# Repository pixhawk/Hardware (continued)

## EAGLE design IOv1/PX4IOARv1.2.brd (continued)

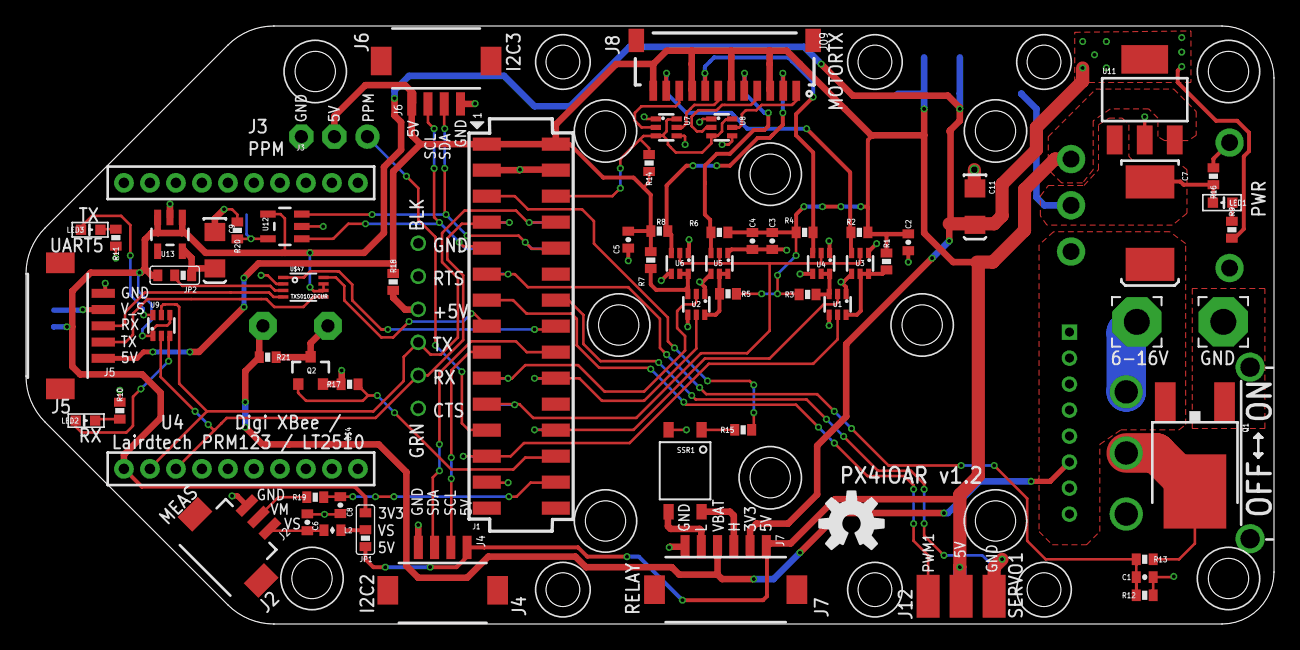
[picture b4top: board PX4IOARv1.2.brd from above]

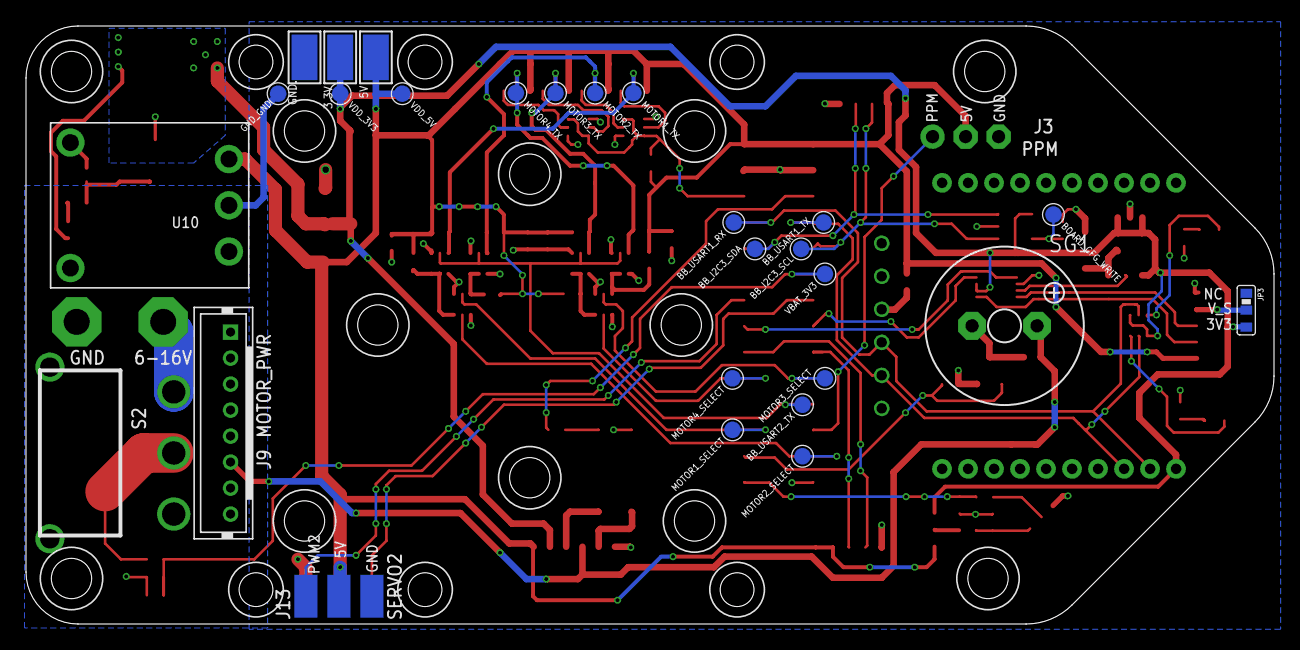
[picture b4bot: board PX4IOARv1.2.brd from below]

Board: 2 copper layers, 96.0 x 46.0 mm, 112 parts (27 on the bottom side), 59 nets.

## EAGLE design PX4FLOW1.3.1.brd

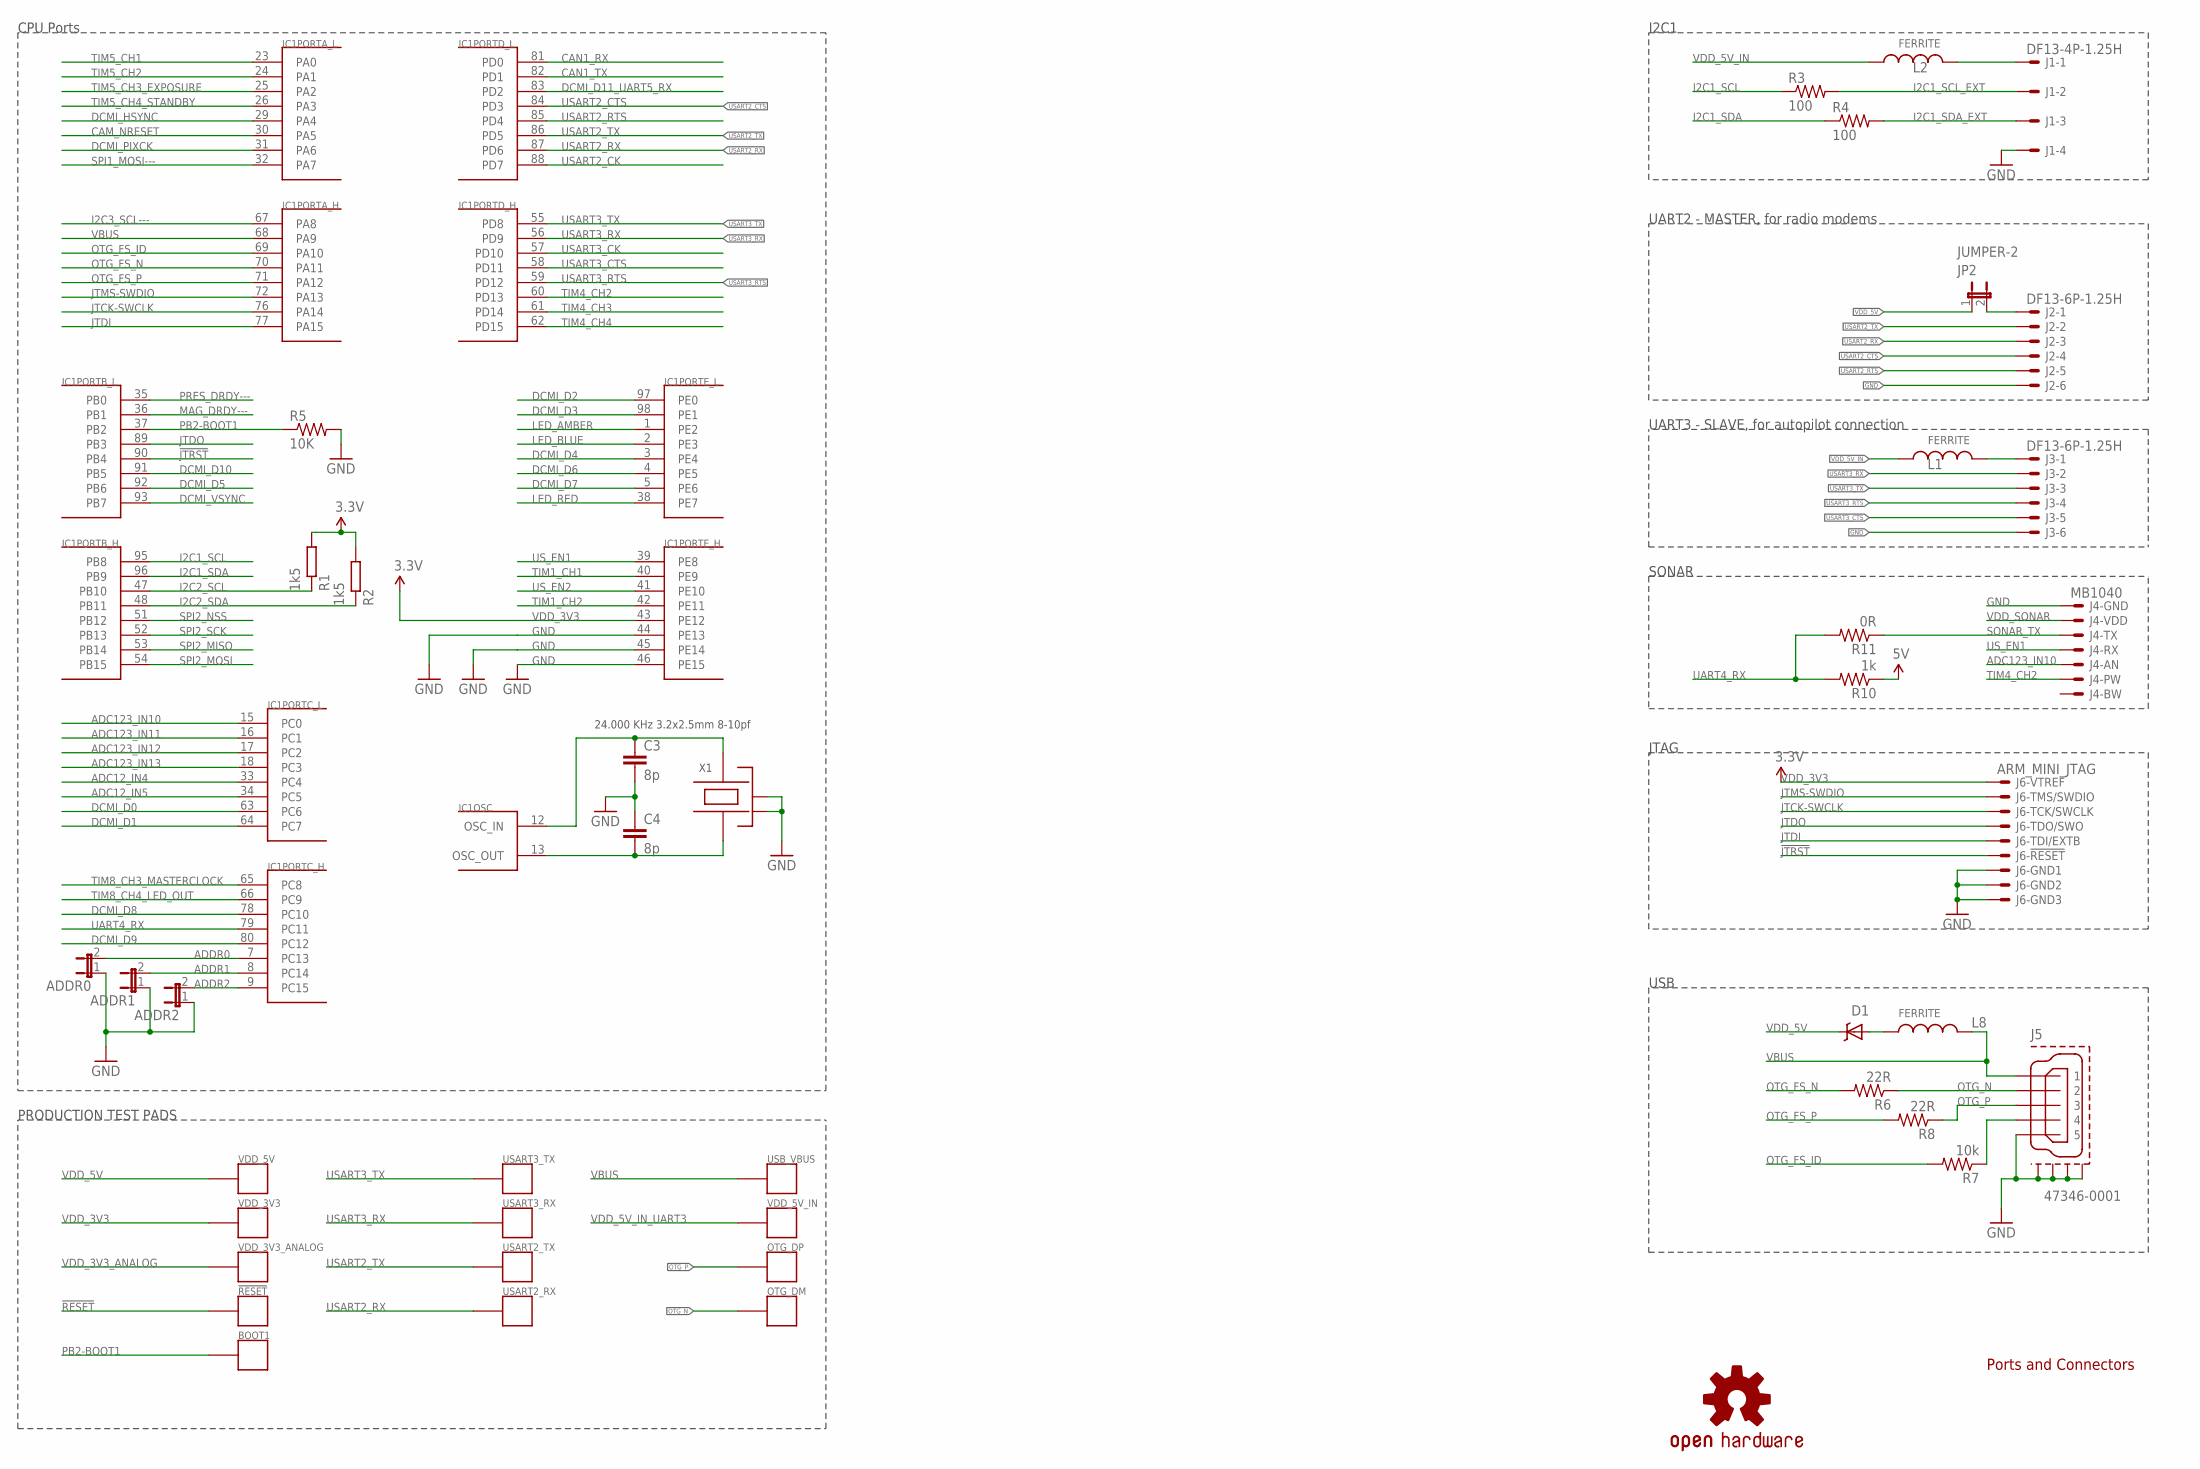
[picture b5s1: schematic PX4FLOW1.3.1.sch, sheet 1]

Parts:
!RESET: PAD.04; PAD.04X.04; PARTNO *
ADDR0, ADDR1, ADDR2: JUMPER-2; SJ_2; PARTNO *
BOOT1: PAD.04; PAD.04X.04; PARTNO *
C3, C4: 8p; 0402-CAP
D1: MSS1P4-M3; MICROSMP; PARTNO MSS1P4-M3/89A
IC1: STM32F4X7VX; TQFP100; PARTNO STM32F407VGT6
J1: DF13-4P-1.25H; DF13A-4P-1.25H; PARTNO DF13A-4P-1.25H(20)
J2, J3: DF13-6P-1.25H; DF13A-6P-1.25H; PARTNO DF13A-6P-1.25H(20)
J4: MB1040; MAXSONAR; PARTNO *
J5: 47346-0001; MOLEX-47346-0001; PARTNO 47346-0001
J6: ARM_MINI_JTAG; FTSH-105-01-XXX-DV-K; PARTNO M50-3900542
JP2: JUMPER-2; SJ_2; PARTNO *
L1, L2, L8: FERRITE; 0402-IND; PARTNO BKP1005HS121-T
OTG_DM: PAD.04; PAD.04X.04; PARTNO *
OTG_DP: PAD.04; PAD.04X.04; PARTNO *
R1, R2: 1k5; 0402-RES
R3, R4: 100; 0402-RES; PARTNO RMCF0402JT100R
R5: 10K; 0402-RES; PARTNO RMCF0402FT10K0
R6, R8: 22R; 0402-RES; PARTNO RMCF0402JT22R0
R7: 10k; 0402-RES; PARTNO MFR-25FBF-10K0
R10: 1k; 0402-RES; PARTNO RMCF0402JT1K00
R11: 0R; 0402-RES; PARTNO RMCF0402JT1K00
U$10: OSHW-LOGOS; OSHW-LOGO-S; PARTNO *
USART2_RX, USART2_TX, USART3_RX, USART3_TX: PAD.04; PAD.04X.04; PARTNO *
USB_VBUS: PAD.04; PAD.04X.04; PARTNO *
VDD_3V3, VDD_3V3_ANALOG, VDD_5V, VDD_5V_IN: PAD.04; PAD.04X.04; PARTNO *
X1: 24.000 KHz 3.2x2.5mm 8-10pf; OSCILLATOR-3.2X2.5; PARTNO NX3225SA-24.000000MHZ

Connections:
!JTRST: IC1.90 (PB4), J6.10
!RESET: !RESET.P$1; also elsewhere on the board
ADC12_IN4: IC1.33 (PC4)
ADC12_IN5: IC1.34 (PC5)
ADC123_IN10: IC1.15 (PC0), J4.AN
ADC123_IN11: IC1.16 (PC1)
ADC123_IN12: IC1.17 (PC2)
ADC123_IN13: IC1.18 (PC3)
ADDR0: ADDR0.2, IC1.7 (PC13)
ADDR1: ADDR1.2, IC1.8 (PC14)
ADDR2: ADDR2.2, IC1.9 (PC15)
CAM_NRESET: IC1.30 (PA5); also elsewhere on the board
CAN1_RX: IC1.81 (PD0)
CAN1_TX: IC1.82 (PD1)
DCMI_D0: IC1.63 (PC6); also elsewhere on the board
DCMI_D1: IC1.64 (PC7); also elsewhere on the board
DCMI_D2: IC1.97 (PE0); also elsewhere on the board
DCMI_D3: IC1.98 (PE1); also elsewhere on the board
DCMI_D4: IC1.3 (PE4); also elsewhere on the board
DCMI_D5: IC1.92 (PB6); also elsewhere on the board
DCMI_D6: IC1.4 (PE5); also elsewhere on the board
DCMI_D7: IC1.5 (PE6); also elsewhere on the board
DCMI_D8: IC1.78 (PC10); also elsewhere on the board
DCMI_D9: IC1.80 (PC12); also elsewhere on the board
DCMI_D10: IC1.91 (PB5)
DCMI_D11_UART5_RX: IC1.83 (PD2)
DCMI_HSYNC: IC1.29 (PA4); also elsewhere on the board
DCMI_PIXCK: IC1.31 (PA6); also elsewhere on the board
DCMI_VSYNC: IC1.93 (PB7); also elsewhere on the board
GND: ADDR0.1, ADDR1.1, ADDR2.1, C3.P$2 (2), C4.P$1 (1), IC1.44 (PE13), IC1.45 (PE14), IC1.46 (PE15), J1.4, J2.6, J3.6, J4.GND, J5.GND (5), J5.GND1, J5.GND2, J5.GND3, J5.GND4, J6.3, J6.5, J6.9, R5.2, X1.2 (NC_2), X1.4 (NC_4); also elsewhere on the board
I2C1_SCL: IC1.95 (PB8), R3.1
I2C1_SCL_EXT: J1.2, R3.2
I2C1_SDA: IC1.96 (PB9), R4.1
I2C1_SDA_EXT: J1.3, R4.2
I2C2_SCL: IC1.47 (PB10), R1.P$1 (1); also elsewhere on the board
I2C2_SDA: IC1.48 (PB11), R2.P$1 (1); also elsewhere on the board
I2C3_SCL---: IC1.67 (PA8)
JTCK-SWCLK: IC1.76 (PA14), J6.4
JTDI: IC1.77 (PA15), J6.8
JTDO: IC1.89 (PB3), J6.6
JTMS-SWDIO: IC1.72 (PA13), J6.2
LED_AMBER: IC1.1 (PE2); also elsewhere on the board
LED_BLUE: IC1.2 (PE3); also elsewhere on the board
LED_RED: IC1.38 (PE7); also elsewhere on the board
MAG_DRDY---: IC1.36 (PB1)
unnamed: C4.P$2 (2), IC1.13 (OSC_OUT), X1.1
unnamed: C3.P$1 (1), IC1.12 (OSC_IN), X1.3
unnamed: J1.1, L2.P$2 (2)
unnamed: J2.1, JP2.2
unnamed: D1.ANODE (A), L8.P$1 (1)
OTG_FS_ID: IC1.69 (PA10), R7.2
OTG_FS_N: IC1.70 (PA11), R6.2
OTG_FS_P: IC1.71 (PA12), R8.2
OTG_ID: J5.ID (4), R7.1
OTG_N: J5.D- (2), OTG_DM.P$1, R6.1
OTG_P: J5.D+ (3), OTG_DP.P$1, R8.1
PB2-BOOT1: BOOT1.P$1, IC1.37 (PB2), R5.1
PRES_DRDY---: IC1.35 (PB0)
SONAR_TX: J4.TX, R11.1
SPI1_MOSI---: IC1.32 (PA7)
SPI2_MISO: IC1.53 (PB14); also elsewhere on the board
SPI2_MOSI: IC1.54 (PB15); also elsewhere on the board
SPI2_NSS: IC1.51 (PB12); also elsewhere on the board
SPI2_SCK: IC1.52 (PB13); also elsewhere on the board
TIM1_CH1: IC1.40 (PE9)
TIM1_CH2: IC1.42 (PE11)
TIM4_CH2: IC1.60 (PD13), J4.PW
TIM4_CH3: IC1.61 (PD14)
TIM4_CH4: IC1.62 (PD15)
TIM5_CH1: IC1.23 (PA0)
TIM5_CH2: IC1.24 (PA1)
TIM5_CH3_EXPOSURE: IC1.25 (PA2); also elsewhere on the board
TIM5_CH4_STANDBY: IC1.26 (PA3); also elsewhere on the board
TIM8_CH3_MASTERCLOCK: IC1.65 (PC8); also elsewhere on the board
TIM8_CH4_LED_OUT: IC1.66 (PC9); also elsewhere on the board
UART4_RX: IC1.79 (PC11), R10.2, R11.2
USART2_CK: IC1.88 (PD7)
USART2_CTS: IC1.84 (PD3), J2.4
USART2_RTS: IC1.85 (PD4), J2.5
USART2_RX: IC1.87 (PD6), J2.3, USART2_RX.P$1
USART2_TX: IC1.86 (PD5), J2.2, USART2_TX.P$1
USART3_CK: IC1.57 (PD10)
USART3_CTS: IC1.58 (PD11), J3.5
USART3_RTS: IC1.59 (PD12), J3.4
USART3_RX: IC1.56 (PD9), J3.2, USART3_RX.P$1
USART3_TX: IC1.55 (PD8), J3.3, USART3_TX.P$1
US_EN1: IC1.39 (PE8), J4.RX
US_EN2: IC1.41 (PE10)
VBUS: IC1.68 (PA9), J5.VBUS (1), L8.P$2 (2), USB_VBUS.P$1
VDD_3V3: IC1.43 (PE12), J6.1, R1.P$2 (2), R2.P$2 (2), VDD_3V3.P$1; also elsewhere on the board
VDD_3V3_ANALOG: VDD_3V3_ANALOG.P$1; also elsewhere on the board
VDD_5V: D1.CATHODE (C), JP2.1, R10.1, VDD_5V.P$1; also elsewhere on the board
VDD_5V_IN: L1.P$1 (1), L2.P$1 (1); also elsewhere on the board
VDD_5V_IN_UART3: J3.1, L1.P$2 (2), VDD_5V_IN.P$1
VDD_SONAR: J4.VDD; also elsewhere on the board

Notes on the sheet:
Ports and Connectors
CPU Ports
I2C1
USB
JTAG
UART2 - MASTER, for radio modems
UART3 - SLAVE, for autopilot connection
SONAR
PRODUCTION TEST PADS

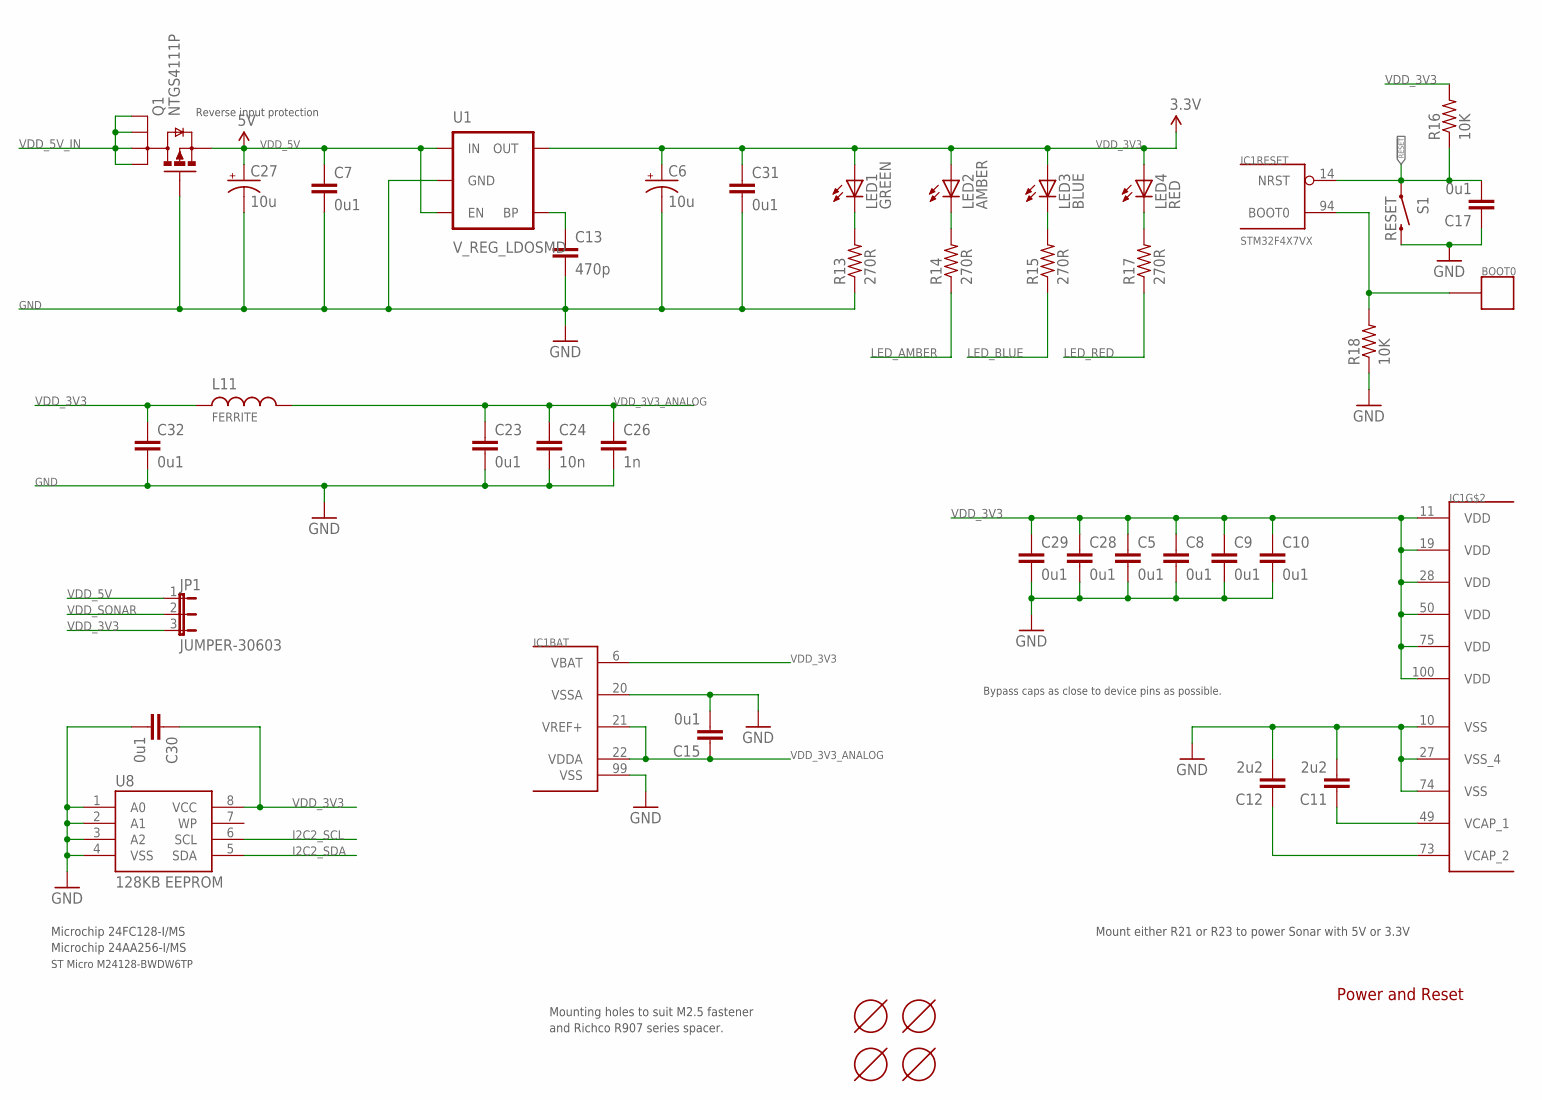
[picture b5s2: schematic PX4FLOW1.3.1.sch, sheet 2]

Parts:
BOOT0: PAD.05; PAD.05X.05; PARTNO *
C5, C7, C8, C9, C10, C15, C17, C23, C28, C29, C30, C31, C32: 0u1; 0402-CAP; PARTNO CC0402ZRY5V7BB104
C6, C27: 10u; EIA3216; PARTNO F931A106MAA
C11, C12: 2u2; 0402-CAP; PARTNO C1608Y5V1C225Z
C13: 470p; 0402-CAP; PARTNO CC0402KRX7R9BB471
C24: 10n; 0402-CAP; PARTNO CC0402ZRY5V7BB104
C26: 1n; 0402-CAP; PARTNO CC0402ZRY5V7BB104
IC1: STM32F4X7VX; TQFP100; PARTNO STM32F407VGT6
JP1: JUMPER-30603; SJ_3_0603_PASTE1&2; PARTNO RMCF0402ZT0R00
L11: FERRITE; 0402-IND; PARTNO BKP1005HS121-T
LED1: GREEN; LED-0603; PARTNO LNJ337W83RA
LED2: AMBER; LED-0603; PARTNO LNJ437W84RA
LED3: BLUE; LED-0603; PARTNO LNJ937W8CRA
LED4: RED; LED-0603; PARTNO LNJ237W82RA
Q1: NTGS4111P; TSOP-6; PARTNO NTGS4111P
R13, R14: 270R; 0402-RES; PARTNO MCR01MZPJ271
R15, R17: 270R; 0402-RES; PARTNO MCR01MZPJ820
R16, R18: 10K; 0402-RES; PARTNO RMCF0402FT10K0
S1: RESET; EVQP7J01K; PARTNO EVQP7J01K
U1: V_REG_LDOSMD; SOT23-5; PARTNO MIC5207-3.3YM5
U8: 128KB EEPROM; MSOP-8; PARTNO 24FC128-I/MS
U$1, U$2, U$3, U$4: MOUNT-HOLE3.1MM; MOUNT-HOLE3.1; PARTNO *

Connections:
!RESET: C17.2, IC1.14 (NRST), R16.1, S1.A1 (1); also elsewhere on the board
BOOT0: BOOT0.P$1, IC1.94 (BOOT0), R18.2
GND: C5.2, C6.C (-), C7.2, C8.2, C9.2, C10.2, C11.2, C12.2, C13.2, C15.2, C17.1, C23.2, C24.2, C26.2, C27.C (-), C28.2, C29.2, C30.2, C31.2, C32.2, IC1.10 (VSS), IC1.20 (VSSA), IC1.27 (VSS_4), IC1.74 (VSS), IC1.99 (VSS), Q1.3 (G), R13.1, R18.1, S1.B3 (2), U1.2 (GND), U8.1 (A0), U8.2 (A1), U8.3 (A2), U8.4 (VSS); also elsewhere on the board
I2C2_SCL: U8.6 (SCL); also elsewhere on the board
I2C2_SDA: U8.5 (SDA); also elsewhere on the board
LED_AMBER: R14.1; also elsewhere on the board
LED_BLUE: R15.1; also elsewhere on the board
LED_RED: R17.1; also elsewhere on the board
unnamed: C13.1, U1.4 (BP)
unnamed: LED4.C, R17.2
unnamed: LED3.C, R15.2
unnamed: LED1.C, R13.2
unnamed: LED2.C, R14.2
VCAP_1: C11.1, IC1.49 (VCAP_1)
VCAP_2: C12.1, IC1.73 (VCAP_2)
VDD_3V3: C5.1, C6.A (+), C8.1, C9.1, C10.1, C28.1, C29.1, C30.1, C31.1, C32.1, IC1.6 (VBAT), IC1.11 (VDD), IC1.19 (VDD), IC1.28 (VDD), IC1.50 (VDD), IC1.75 (VDD), IC1.100 (VDD), JP1.3, L11.P$1 (1), LED1.A, LED2.A, LED3.A, LED4.A, R16.2, U1.5 (OUT), U8.8 (VCC); also elsewhere on the board
VDD_3V3_ANALOG: C15.1, C23.1, C24.1, C26.1, IC1.21 (VREF+), IC1.22 (VDDA), L11.P$2 (2); also elsewhere on the board
VDD_5V: C7.1, C27.A (+), JP1.1, Q1.4 (S), U1.1 (IN), U1.3 (EN); also elsewhere on the board
VDD_5V_IN: Q1.1 (D), Q1.2 (D1), Q1.5 (D2), Q1.6 (D3); also elsewhere on the board
VDD_SONAR: JP1.2; also elsewhere on the board

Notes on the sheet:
Power and Reset
Microchip 24FC128-I/MS
Microchip 24AA256-I/MS
Mounting holes to suit M2.5 fastener
and Richco R907 series spacer.
ST Micro M24128-BWDW6TP
Reverse input protection
Mount either R21 or R23 to power Sonar with 5V or 3.3V
Bypass caps as close to device pins as possible.

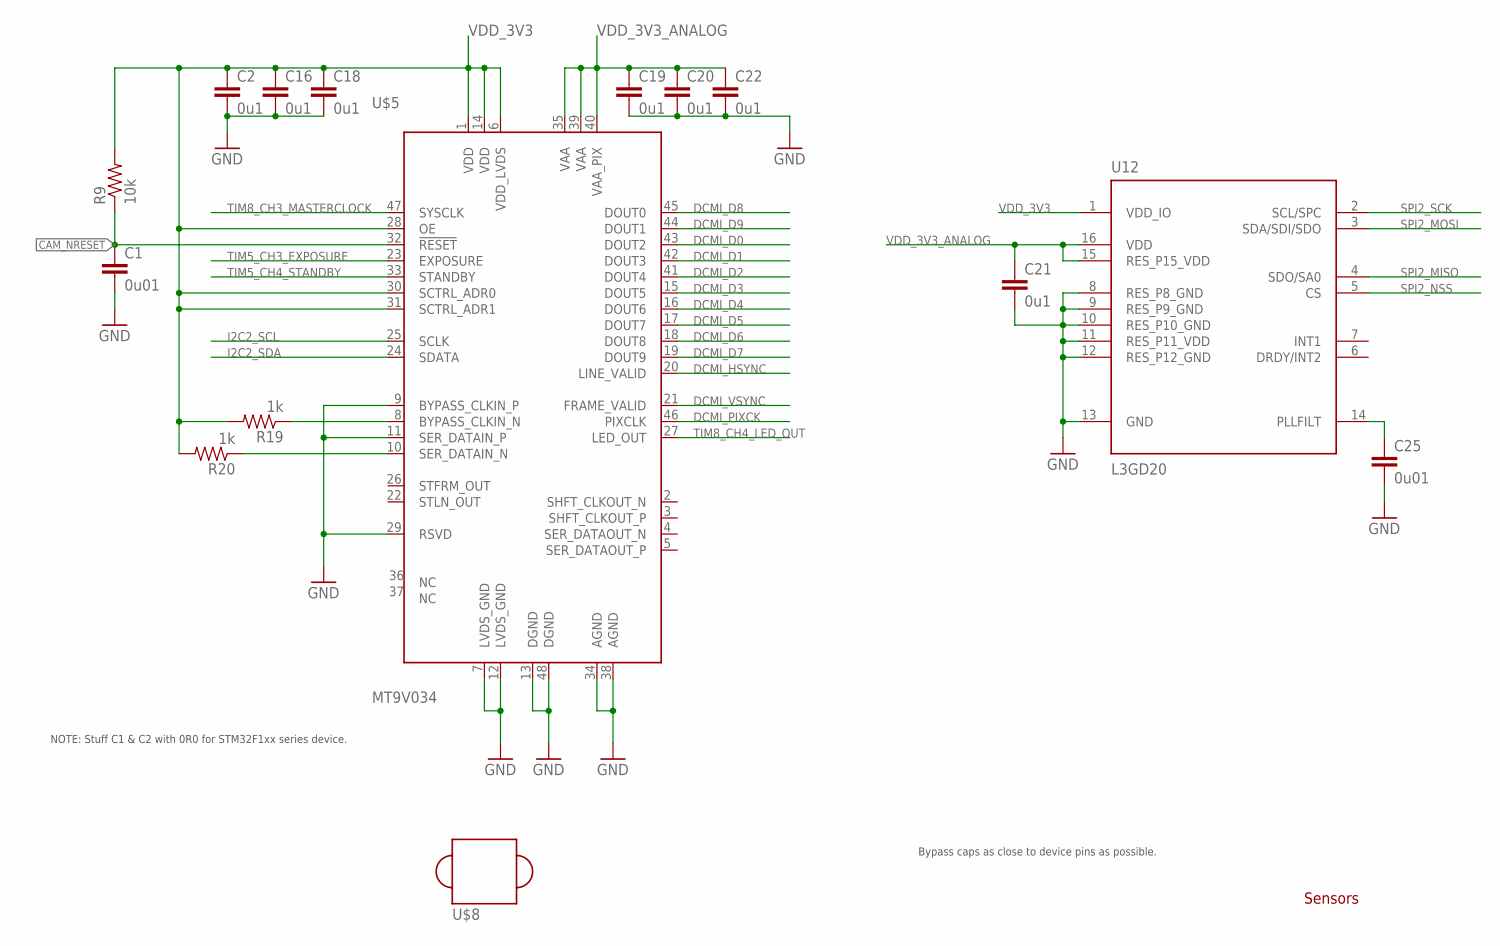
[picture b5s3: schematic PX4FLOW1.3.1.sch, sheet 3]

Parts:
C1, C25: 0u01; 0402-CAP; PARTNO CC0402KRX7R7BB103
C2, C16, C18, C19, C20, C21, C22: 0u1; 0402-CAP; PARTNO CC0402ZRY5V7BB104
R9: 10k; 0402-RES; PARTNO MCR01MZPJ271
R19, R20: 1k; 0402-RES; PARTNO RMCF0402JT1K00
U12: L3GD20; L3G4200DH-MAN; PARTNO L3GD20
U$5: MT9V034; CLCC-48; PARTNO MT9V034C12STM
U$8: LENSMOUNT_M12; LENSMOUNT_LARGE_M12; PARTNO *

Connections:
CAM_NRESET: C1.1, R9.1, U$5.32 (!RESET); also elsewhere on the board
DCMI_D0: U$5.43 (DOUT2); also elsewhere on the board
DCMI_D1: U$5.42 (DOUT3); also elsewhere on the board
DCMI_D2: U$5.41 (DOUT4); also elsewhere on the board
DCMI_D3: U$5.15 (DOUT5); also elsewhere on the board
DCMI_D4: U$5.16 (DOUT6); also elsewhere on the board
DCMI_D5: U$5.17 (DOUT7); also elsewhere on the board
DCMI_D6: U$5.18 (DOUT8); also elsewhere on the board
DCMI_D7: U$5.19 (DOUT9); also elsewhere on the board
DCMI_D8: U$5.45 (DOUT0); also elsewhere on the board
DCMI_D9: U$5.44 (DOUT1); also elsewhere on the board
DCMI_HSYNC: U$5.20 (LINE_VALID); also elsewhere on the board
DCMI_PIXCK: U$5.46 (PIXCLK); also elsewhere on the board
DCMI_VSYNC: U$5.21 (FRAME_VALID); also elsewhere on the board
GND: C1.2, C2.2, C16.2, C18.2, C19.2, C20.2, C21.2, C22.2, C25.2, U12.8 (RES_P8_GND), U12.9 (RES_P9_GND), U12.10 (RES_P10_GND), U12.11 (RES_P11_VDD), U12.12 (RES_P12_GND), U12.13 (GND), U$5.7 (LVDS_GND), U$5.9 (BYPASS_CLKIN_P), U$5.11 (SER_DATAIN_P), U$5.12 (LVDS_GND), U$5.13 (DGND), U$5.29 (RSVD), U$5.34 (AGND), U$5.38 (AGND), U$5.48 (DGND); also elsewhere on the board
I2C2_SCL: U$5.25 (SCLK); also elsewhere on the board
I2C2_SDA: U$5.24 (SDATA); also elsewhere on the board
unnamed: R19.1, U$5.8 (BYPASS_CLKIN_N)
unnamed: R20.1, U$5.10 (SER_DATAIN_N)
unnamed: C25.1, U12.14 (PLLFILT)
SPI2_MISO: U12.4 (SDO/SA0); also elsewhere on the board
SPI2_MOSI: U12.3 (SDA/SDI/SDO); also elsewhere on the board
SPI2_NSS: U12.5 (CS); also elsewhere on the board
SPI2_SCK: U12.2 (SCL/SPC); also elsewhere on the board
TIM5_CH3_EXPOSURE: U$5.23 (EXPOSURE); also elsewhere on the board
TIM5_CH4_STANDBY: U$5.33 (STANDBY); also elsewhere on the board
TIM8_CH3_MASTERCLOCK: U$5.47 (SYSCLK); also elsewhere on the board
TIM8_CH4_LED_OUT: U$5.27 (LED_OUT); also elsewhere on the board
VDD_3V3: C2.1, C16.1, C18.1, R9.2, R19.2, R20.2, U12.1 (VDD_IO), U$5.1 (VDD), U$5.6 (VDD_LVDS), U$5.14 (VDD), U$5.28 (OE), U$5.30 (SCTRL_ADR0), U$5.31 (SCTRL_ADR1); also elsewhere on the board
VDD_3V3_ANALOG: C19.1, C20.1, C21.1, C22.1, U12.15 (RES_P15_VDD), U12.16 (VDD), U$5.35 (VAA), U$5.39 (VAA), U$5.40 (VAA_PIX); also elsewhere on the board

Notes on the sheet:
Sensors
Bypass caps as close to device pins as possible.
NOTE: Stuff C1 & C2 with 0R0 for STM32F1xx series device.

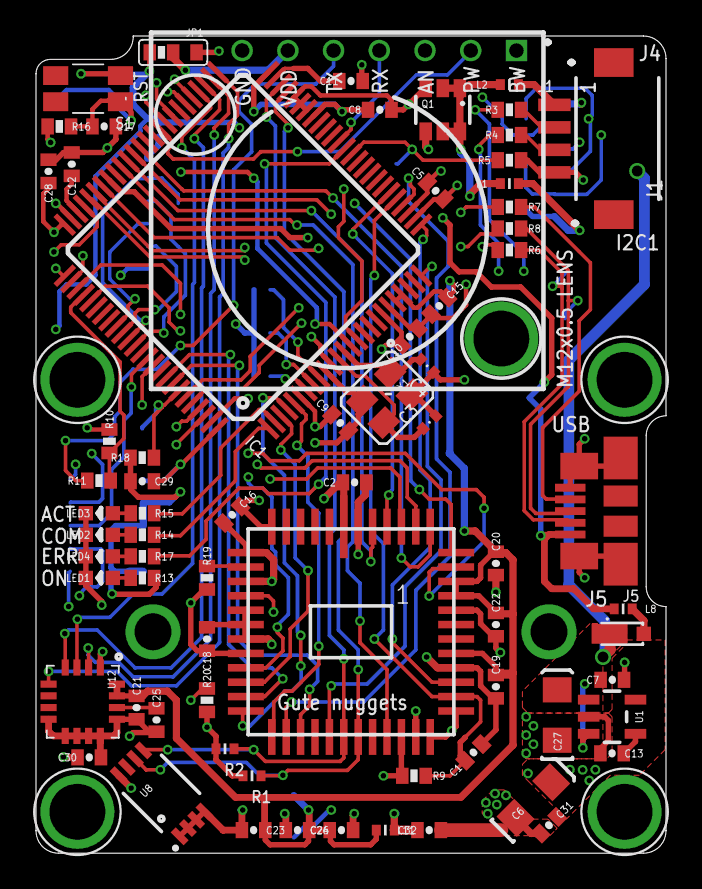
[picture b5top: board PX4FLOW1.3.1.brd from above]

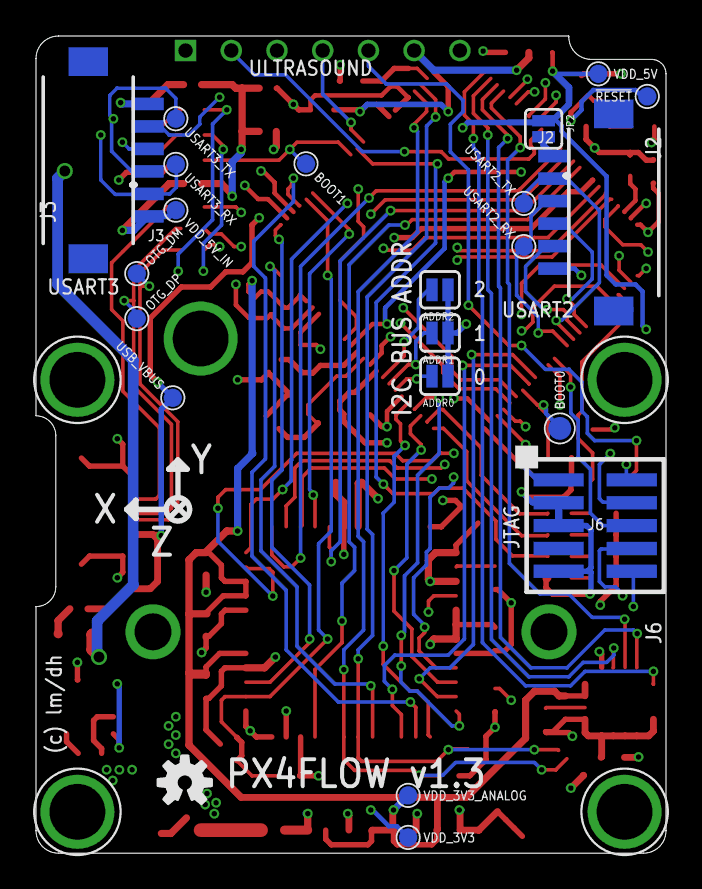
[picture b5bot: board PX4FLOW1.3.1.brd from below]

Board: 4 copper layers, 35.0 x 45.4 mm, 98 parts (22 on the bottom side), 84 nets.
